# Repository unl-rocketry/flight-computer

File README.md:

# Flight Computer
A versatile, inexpensive, modular, and **open source** flight computer and altimeter
system for amateur and experimental rocketry.

All designs in this repository are licensed under the [**CERN-OHL-S v2 or any later 
version**](https://ohwr.org/project/cernohl/-/wikis/uploads/b236492596cfc91c12def7d50bbf7da0/cern_ohl_s_v2.pdf). 
Contributions are welcome!

# Core Board
This design should be capable of using input voltages from 3v → 16v on the
battery input to allow for a wide range of batteries to be used. It is designed
to control and independently fire up to 3 individual high power in-flight events
(eg. ejection charges).

## Built-in Sensors
The sensor package includes a Bosch BNO055 motion co-processor for acceleration,
magnetic heading, and 3d orientation. It also includes a Bosch BME280 sensor for
pressure (along with altitude), temperature, and humidity measurements. These
sensor measurements can be used for flight control, and can also be logged to a
MicroSD card mounted on the board for ease of data recovery.

## Toolchain Support
All programmable components of this board were selected to be compatible with
Rust-based microcontroller frameworks like Embassy, for ease of programming and
future extension of software capabilities.

## Images

# Expansion Modules
A major feature of the Core Board is the ability to be expanded by
connecting via an I2C (and hopefully in the future CAN Bus) connection to other
boards and sensors with the same connectors. These expansion  boards could
provide additional capabilities while being modular for quickly swapping and
replacing parts.

The connectors on the Core Board are compatible with any Adafruit Stemma QT or 
SparkFun Qwiic board, which immediately provides for a lot of options for
sensors without any design or soldering work needed.

In the future, this repository will host the KiCad files for expansion boards
created by UNL Aerospace Rocketry.

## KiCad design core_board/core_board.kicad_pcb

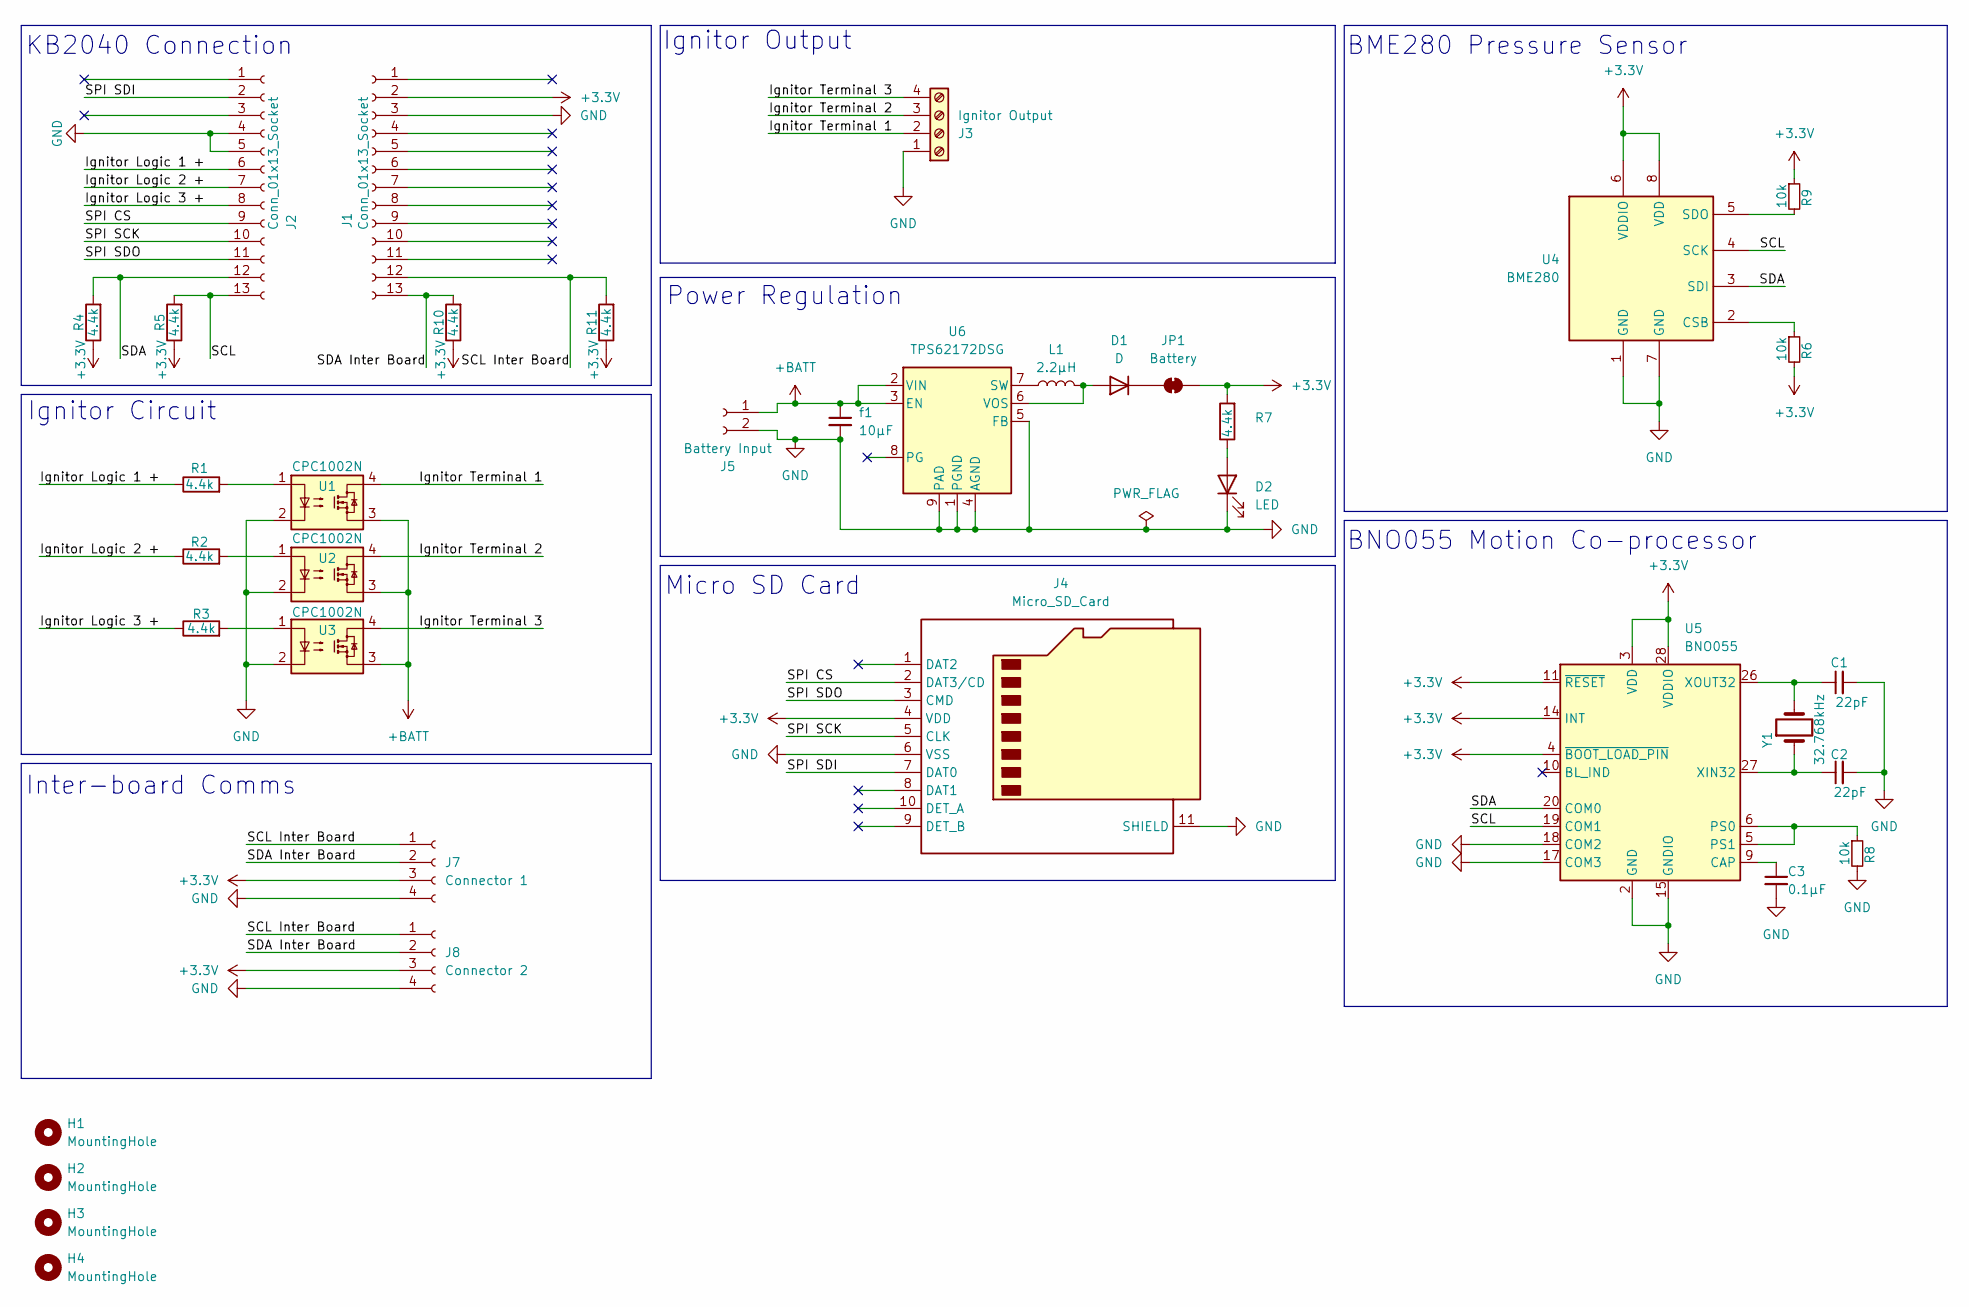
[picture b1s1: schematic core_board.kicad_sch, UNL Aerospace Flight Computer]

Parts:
C1, C2: 22pF; C_0603_1608Metric_Pad1.08x0.95mm_HandSolder
C3: 0.1µF; C_0603_1608Metric_Pad1.08x0.95mm_HandSolder
D1: D; D_0603_1608Metric_Pad1.05x0.95mm_HandSolder
D2: LED; LED_0603_1608Metric_Pad1.05x0.95mm_HandSolder
H1, H2, H3, H4: MountingHole; MountingHole_2.2mm_M2_ISO7380_Pad
J1, J2: Conn_01x13_Socket; PinHeader_1x13_P2.54mm_Vertical
J3: Ignitor Output; TerminalBlock_Phoenix_MPT-0,5-4-2.54_1x04_P2.54mm_Horizontal
J4: Micro_SD_Card; microSD_HC_Hirose_DM3D-SF
J5: Battery Input; JST_PH_S2B-PH-K_1x02_P2.00mm_Horizontal
J7: Connector 1; JST_SH_BM04B-SRSS-TB_1x04-1MP_P1.00mm_Vertical-CUSTOM
J8: Connector 2; JST_SH_BM04B-SRSS-TB_1x04-1MP_P1.00mm_Vertical-CUSTOM
JP1: Battery; SolderJumper-2_P1.3mm_Bridged_Pad1.0x1.5mm
L1: 2.2µH; L_0603_1608Metric_Pad1.05x0.95mm_HandSolder
R1, R2, R3, R4, R5, R7, R10, R11: 4.4k; R_0603_1608Metric_Pad0.98x0.95mm_HandSolder
R6, R8, R9: 10k; R_0603_1608Metric_Pad0.98x0.95mm_HandSolder
U1, U2, U3: CPC1002N; SOP-4_3.8x4.1mm_P2.54mm
U4: BME280; Bosch_LGA-8_2.5x2.5mm_P0.65mm_ClockwisePinNumbering
U5: BNO055; LGA-28_5.2x3.8mm_P0.5mm
U6: TPS62172DSG; WSON-8-1EP_2x2mm_P0.5mm_EP0.9x1.6mm_ThermalVias
Y1: 32.768kHz; Crystal_SMD_G8-2Pin_3.2x1.5mm_HandSoldering
f1: 10µF; C_0805_2012Metric_Pad1.18x1.45mm_HandSolder

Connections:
+3.3V: J1.2, J4.4 (VDD), J7.3, J8.3, JP1.2 (B), R4.1, R5.1, R6.2, R7.2, R9.1, R10.1, R11.1, U4.6 (VDDIO), U4.8 (VDD), U5.3 (VDD), U5.4 (~BOOT_LOAD_PIN), U5.11 (~RESET), U5.14 (INT), U5.28 (VDDIO)
+BATT: J5.1, U1.3, U2.3, U3.3, U6.2 (VIN), U6.3 (EN), f1.1
/Ignitor Logic 1 +: J2.6, R1.1
/Ignitor Logic 2 +: J2.7, R2.1
/Ignitor Logic 3 +: J2.8, R3.1
/Ignitor Terminal 1: J3.2, U1.4
/Ignitor Terminal 2: J3.3, U2.4
/Ignitor Terminal 3: J3.4, U3.4
/SCL: J2.13, R5.2, U4.4 (SCK), U5.19 (COM1)
/SCL Inter Board: J1.12, J7.1, J8.1, R11.2
/SDA: J2.12, R4.2, U4.3 (SDI), U5.20 (COM0)
/SDA Inter Board: J1.13, J7.2, J8.2, R10.2
/SPI CS: J2.9, J4.2 (DAT3/CD)
/SPI SCK: J2.10, J4.5 (CLK)
/SPI SDI: J2.2, J4.7 (DAT0)
/SPI SDO: J2.11, J4.3 (CMD)
GND: C1.2, C2.2, C3.2, D2.1 (K), J1.3, J2.4, J2.5, J3.1, J4.6 (VSS), J4.11 (SHIELD), J5.2, J7.4, J8.4, R8.2, U1.2, U2.2, U3.2, U4.1 (GND), U4.7 (GND), U5.2 (GND), U5.15 (GNDIO), U5.16 (GNDIO), U5.17 (COM3), U5.18 (COM2), U5.25 (GNDIO), U6.1 (PGND), U6.4 (AGND), U6.5 (FB), U6.9 (PAD), f1.2
unnamed: D1.2 (A), L1.2, U6.6 (VOS)
unnamed: D1.1 (K), JP1.1 (A)
unnamed: D2.2 (A), R7.1
unnamed: R1.2, U1.1
unnamed: R2.2, U2.1
unnamed: R3.2, U3.1
unnamed: R6.1, U4.2 (CSB)
unnamed: R9.2, U4.5 (SDO)
unnamed: C3.1, U5.9 (CAP)
unnamed: R8.1, U5.5 (PS1), U5.6 (PS0)
unnamed: C2.1, U5.27 (XIN32), Y1.1
unnamed: C1.1, U5.26 (XOUT32), Y1.2
unnamed: L1.1, U6.7 (SW)

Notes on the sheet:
Inter-board Comms
Micro SD Card
Ignitor Circuit
Power Regulation
KB2040 Connection
BME280 Pressure Sensor
Ignitor Output
BNO055 Motion Co-processor

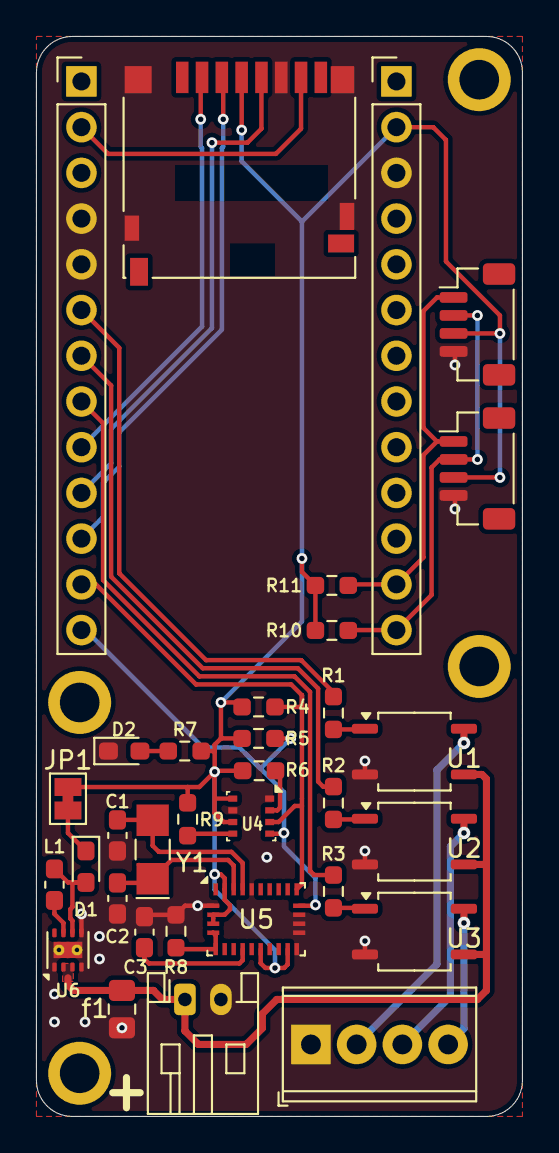
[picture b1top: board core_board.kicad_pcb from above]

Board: 2 copper layers, 27.0 x 60.0 mm, 37 parts (0 on the bottom side), 30 nets.

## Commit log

2024-08-02 Layout finished for BNO055 and BME280
2024-08-02 Completed sensor layout
2024-08-02 Added voltage regulator
2024-08-02 Improved layout of connectors
2024-08-03 Added MicroSD card slot
2024-08-03 Added inter-board connectors to i2c
2024-08-04 Fixed back coppper layer island
2024-08-04 Improved README.md
2024-08-20 Create LICENSE - CERN-OHL-S
2024-08-20 Moved Core board to new folder
2024-08-31 Fixed connector compatibility with STEMMA QT and Qwiic
2024-08-31 Corrected DRC errors
2024-08-31 Set up files for easy fabrication output
2024-09-03 Added Aerospace Club logo and gave mounting holes pads
2024-09-16 Added ground fill to top layer
2024-11-25 Fixed small potential issues
2024-11-26 Tweaked mounting holes, removed warning on back
2024-11-26 Added open hardware logo
2024-11-26 Update README.md
    Updated readme with current information and images
2024-11-27 Improved PCB layout some more
